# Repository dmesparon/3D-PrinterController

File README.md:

# 3D-PrinterController
3D Printer controller based off ATSAM3X8E with onboard Raspberry PI compute module

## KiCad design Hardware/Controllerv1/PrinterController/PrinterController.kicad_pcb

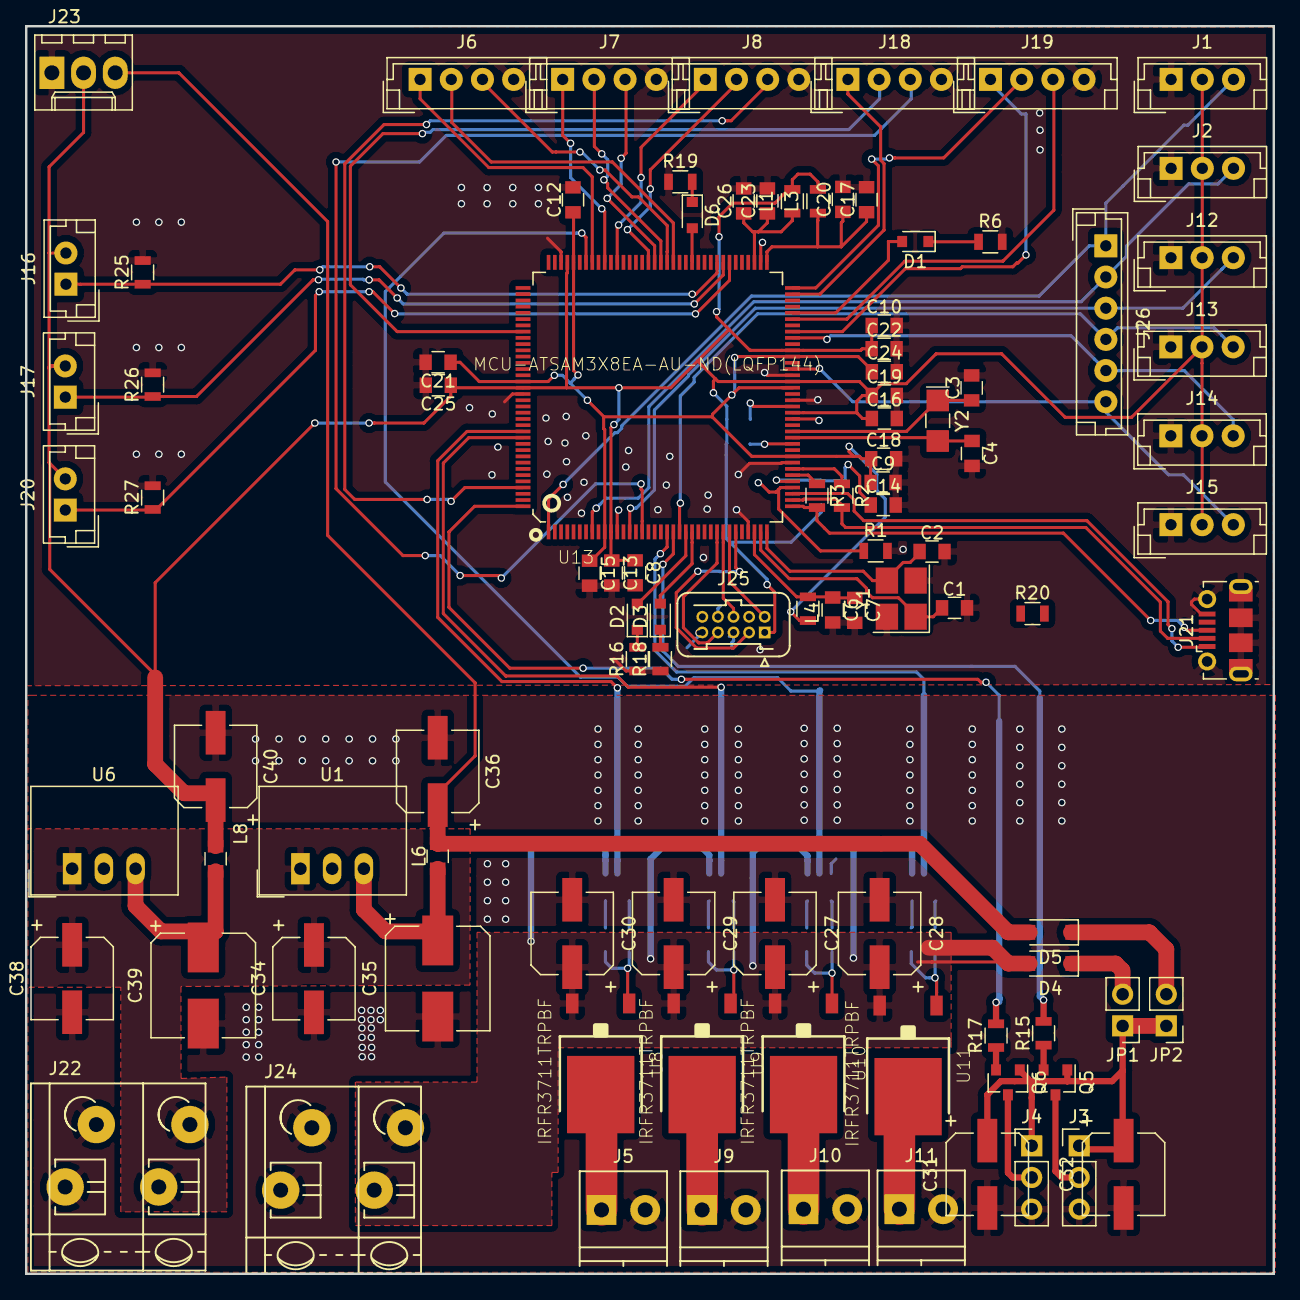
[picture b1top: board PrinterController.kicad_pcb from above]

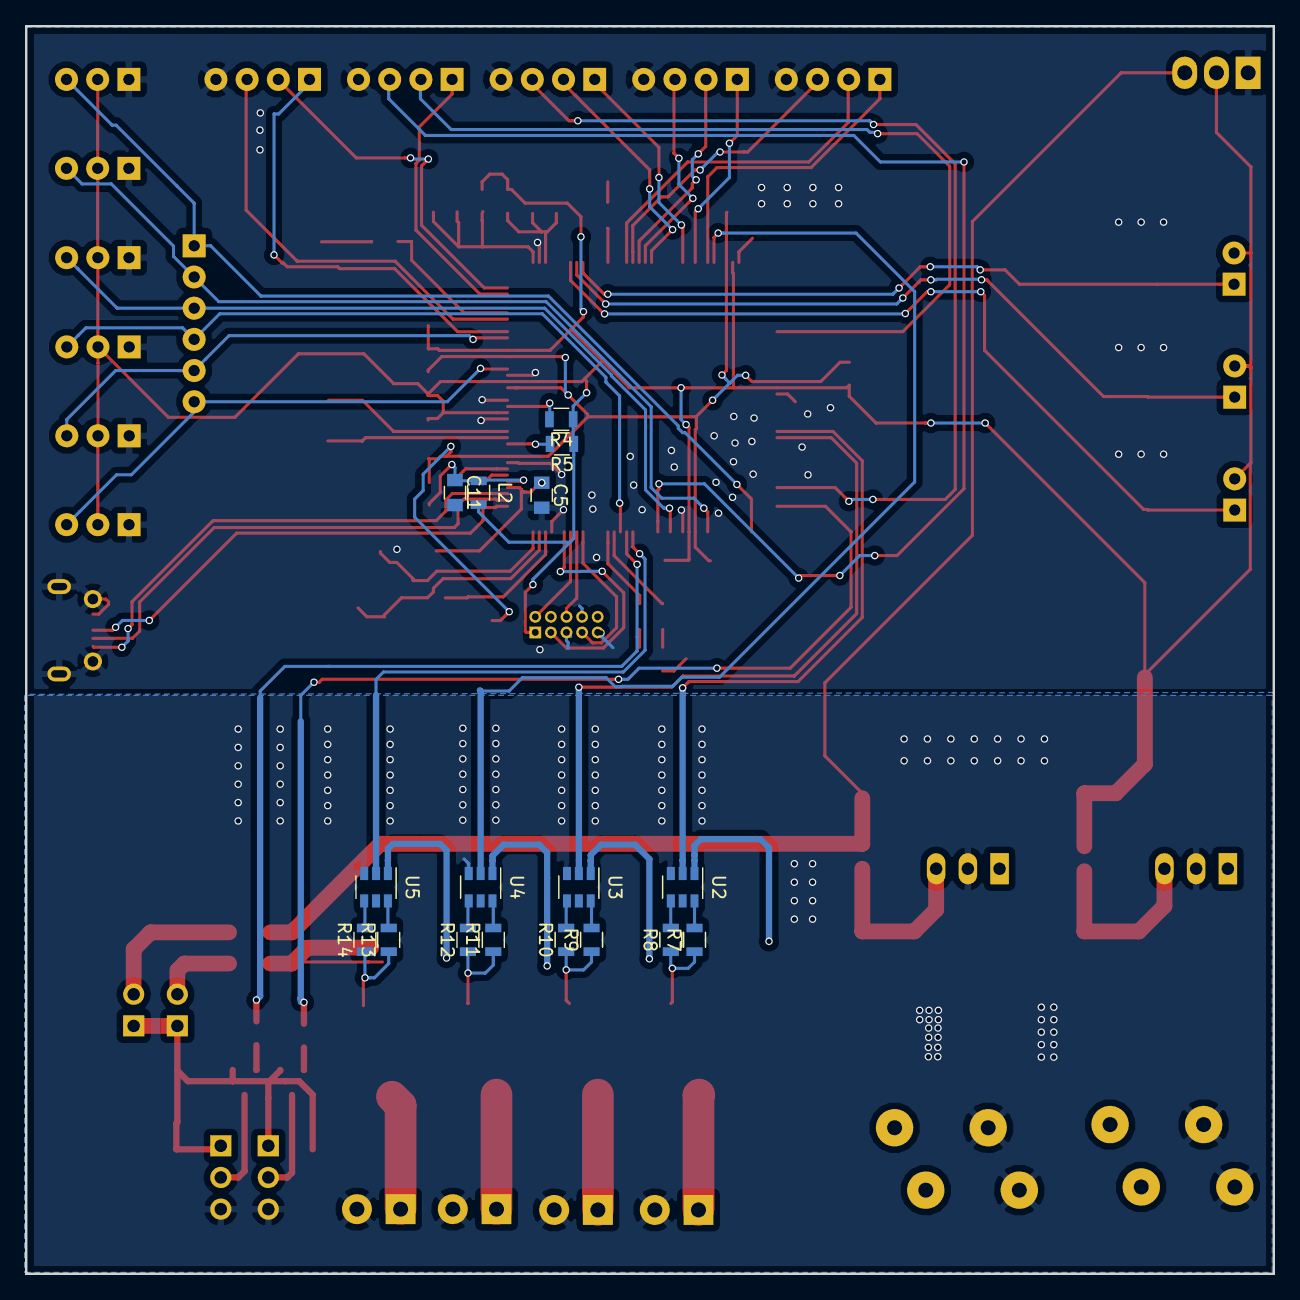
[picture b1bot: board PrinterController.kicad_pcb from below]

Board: 2 copper layers, 100.0 x 100.0 mm, 116 parts (17 on the bottom side), 90 nets.

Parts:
C1, C2, C3, C4: 22p; C_0805
C5: 10p; C_0805
C6, C8, C12, C13, C14, C15, C16, C18, C19, C20, C21, C22, C24, C25, C26: 0.1u; C_0805
C7, C9, C10, C11, C17, C23: 10u; C_0805
C27, C28, C29, C30, C31, C32: 47u; CP_Elec_6.3x5.3
C34, C36, C38, C40: 100u; CP_Elec_6.3x7.7
C35, C39: 470u; CP_Elec_8x10
D1, D2, D3, D6: LED; D_0805
D4, D5: D; D_SOD-123
J1, J2, J12, J13, J14, J15: Conn_01x03; JST_EH_B03B-EH-A_03x2.50mm_Straight
J3, J4: Conn_01x03; Pin_Header_Straight_1x03_Pitch2.54mm
J5, J9, J10, J11: Screw_Terminal_01x02; TerminalBlock_Phoenix_PT-3.5mm_2pol
J6, J7, J8, J18, J19: Conn_01x04; JST_EH_B04B-EH-A_04x2.50mm_Straight
J16, J17, J20: Conn_01x02; JST_EH_B02B-EH-A_02x2.50mm_Straight
J21: USB_OTG; USB_Micro-B_Molex-105017-0001
J22, J24: Screw_Terminal_01x02; TerminalBlock_WAGO-804_RM7.5mm_2pol
J23: Conn_01x03; Molex_KK-6410-03_03x2.54mm_Straight
J25: Conn_ARM_JTAG_SWD_10; Harwin_Gecko-G125-FVX1005L0X_2x05x1.25mm_Straight
J26: Conn_01x06; JST_EH_B06B-EH-A_06x2.50mm_Straight
JP1, JP2: Jumper_NC_Small; Pin_Header_Straight_1x02_Pitch2.54mm
L1, L2, L3, L4: Ferrite_Bead; L_0805
L6, L8: 1u; C_0805
Q5, Q6: Q_NMOS_DGS; SOT-23
R1: 6k8; R_0805
R2, R3: 39; R_0805
R4, R5, R7, R8, R9, R10, R11, R12, R13, R14, R15, R17: 10k; R_0805
R6, R16, R18, R19, R20: 330R; R_0805
R25, R26, R27: 100K; R_0805
U1: R-78E5.0-1.0; DCDC-Conv_RECOM_R-78E-0.5
U2, U3, U4, U5: ZXGD3003E6; SOT-23-6
U6: R-78E3.3-1.0; DCDC-Conv_RECOM_R-78E-0.5
U8, U9, U10, U11: IRFR3711TRPBF; TO252
U13: MCU-ATSAM3X8EA-AU-ND(LQFP144); LQFP144-0.5-20X20M
Y1: Crystal_GND24; Crystal_SMD_3225-4pin_3.2x2.5mm_HandSoldering
Y2: 32.768; Crystal_SMD_MicroCrystal_CC7V-T1A-2pin_3.2x1.5mm_HandSolder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

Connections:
+3V3: C8.1, C10.1, C13.1, C16.1, C19.1, C22.1, C25.1, C40.1, J1.2, J2.2, J12.2, J13.2, J14.2, J15.2, J16.2, J17.2, J20.2, J23.2, J25.1, L1.2, L2.2, L3.2, L8.2, R4.1, R5.1, U13.11, U13.52, U13.57, U13.62, U13.105, U13.125
+5V: C36.1, D5.2, J23.3, L6.2
+VDC: C27.1, C28.1, C29.1, C30.1, D4.2, J24.2, U2.1, U3.1, U4.1, U5.1, U8.2, U9.2, U10.2, U11.2
/DriverStage/FAN1: R15.2, U13.21
/DriverStage/FAN2: R17.2, U13.144
/DriverStage/HEATER1: U2.2, U13.132
/DriverStage/HEATER1_PWR: J5.1, U8.3
/DriverStage/HEATER2: U3.2, U13.133
/DriverStage/HEATER2_PWR: J9.1, U9.3
/DriverStage/HEATER3: U4.2, U13.102
/DriverStage/HEATER3_PWR: J10.1, U10.3
/DriverStage/HEATER4: U5.2, U13.20
/DriverStage/HEATER4_PWR: J11.1, U11.3
/Microcontroller/E0DIR: J18.3, U13.16
/Microcontroller/E0ENABLE: J18.1, U13.71
/Microcontroller/E0STEP: J18.2, U13.116
/Microcontroller/E1DIR: J19.3, U13.67
/Microcontroller/E1ENABLE: J19.1, U13.65
/Microcontroller/E1STEP: J19.2, U13.72
/Microcontroller/TEMP1: J16.1, R25.1, U13.81
/Microcontroller/TEMP2: J17.1, R26.1, U13.80
/Microcontroller/TEMP3: J20.1, R27.1, U13.79
/Microcontroller/VDDANA: C17.1, C20.1, L3.1, U13.73
/Microcontroller/VDDMI: C11.1, C14.1, L2.1, U13.41
/Microcontroller/VDDREF: C23.1, C26.1, L1.1, U13.75
/Microcontroller/XDIR: J6.3, U13.89
/Microcontroller/XENABLE: J6.1, U13.101
/Microcontroller/XSTEP: J6.2, U13.88
/Microcontroller/YDIR: J7.3, U13.91
/Microcontroller/YENABLE: J7.1, U13.99
/Microcontroller/YSTEP: J7.2, U13.90
/Microcontroller/ZDIR: J8.3, U13.141
/Microcontroller/ZENABLE: J8.1, U13.97
/Microcontroller/ZSTEP: J8.2, U13.92
/Motor Connections/ESX1: J1.3, J26.1, U13.1
/Motor Connections/ESX2: J13.3, J26.4, U13.22
/Motor Connections/ESY1: J2.3, J26.2, U13.8
/Motor Connections/ESY2: J14.3, J26.5, U13.64
/Motor Connections/ESZ1: J12.3, J26.3, U13.14
/Motor Connections/ESZ2: J15.3, J26.6, U13.59
GND: C1.2, C2.2, C3.2, C4.2, C5.2, C6.2, C7.2, C8.2, C9.2, C10.2, C11.2, C12.2, C13.2, C14.2, C15.2, C16.2, C17.2, C18.2, C19.2, C20.2, C21.2, C22.2, C23.2, C24.2, C25.2, C26.2, J1.1, J2.1, J6.4, J7.4, J8.4, J12.1, J13.1, J14.1, J15.1, J18.4, J19.4, J21.5, J21.6, J23.1, J25.3, J25.5, J25.9, R1.2, R6.2, R16.1, R18.1, R19.1, R25.2, R26.2, R27.2, U13.12, U13.33, U13.44, U13.51, U13.54, U13.58, U13.74, U13.106, U13.126, Y1.2, Y1.4
GNDPWR: C27.2, C28.2, C29.2, C30.2, C31.2, C32.2, C34.2, C35.2, C36.2, C38.2, C39.2, C40.2, J3.3, J4.3, J5.2, J9.2, J10.2, J11.2, J22.1, J24.1, U1.2, U2.3, U3.3, U4.3, U5.3, U6.2
unnamed: C1.1, U13.35, Y1.1
unnamed: C2.1, U13.36, Y1.3
unnamed: C3.1, U13.49, Y2.1
unnamed: C4.1, U13.48, Y2.2
unnamed: C5.1, R1.1, U13.40
unnamed: C6.1, C7.1, L4.1, U13.34
unnamed: C31.1, C32.1, J3.1, J4.1, JP1.1, JP2.1, Q5.1, Q6.1
unnamed: C35.1, L6.1, U1.3
unnamed: C39.1, L8.1, U6.3
unnamed: D1.1, R6.1
unnamed: D1.2, U13.68
unnamed: D2.1, R16.2
unnamed: D2.2, U13.23
unnamed: D3.1, R18.2
unnamed: D3.2, U13.24
unnamed: D4.1, JP1.2
unnamed: D5.1, JP2.2
unnamed: D6.1, R19.2
unnamed: D6.2, U13.85
unnamed: J3.2, Q5.3
unnamed: J4.2, Q6.3
unnamed: J21.2, R2.2, U13.38
unnamed: J21.3, R3.2, U13.37
unnamed: J25.2, U13.31
unnamed: J25.4, U13.28
unnamed: J25.6, U13.30
unnamed: J25.8, U13.29
unnamed: Q5.2, R15.1
unnamed: Q6.2, R17.1
unnamed: R2.1, U13.43
unnamed: R3.1, U13.42
unnamed: R4.2, U13.53
unnamed: R5.2, U13.47
unnamed: R7.1, R8.1, U8.1
unnamed: R7.2, U2.6
unnamed: R8.2, U2.4
unnamed: R9.2, U3.6
unnamed: R9.1, R10.1, U9.1
unnamed: R10.2, U3.4
unnamed: R11.1, R12.1, U10.1
unnamed: R11.2, U4.6
unnamed: R12.2, U4.4
unnamed: R13.1, R14.1, U11.1
unnamed: R13.2, U5.6
unnamed: R14.2, U5.4
VAA: C34.1, C38.1, J22.2, U1.1, U6.1
VBUS: J21.1, U13.39
VDD: C9.1, C12.1, C15.1, C18.1, C21.1, C24.1, L4.2, U13.10, U13.45, U13.56, U13.61, U13.104, U13.124

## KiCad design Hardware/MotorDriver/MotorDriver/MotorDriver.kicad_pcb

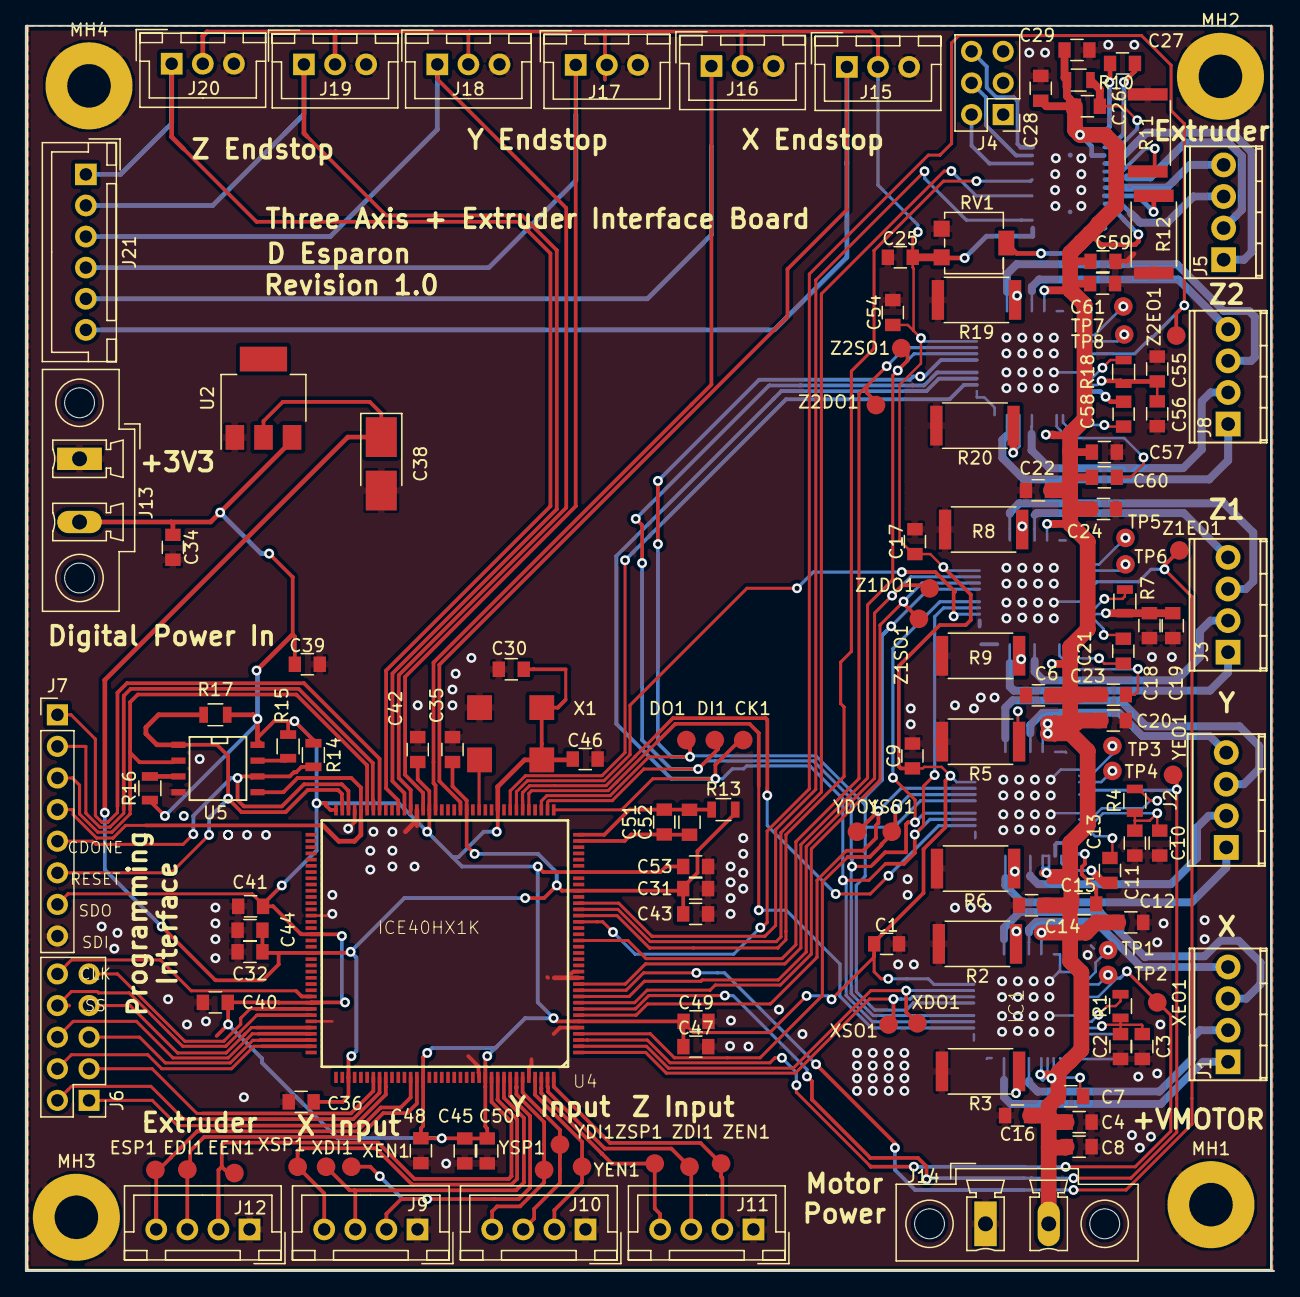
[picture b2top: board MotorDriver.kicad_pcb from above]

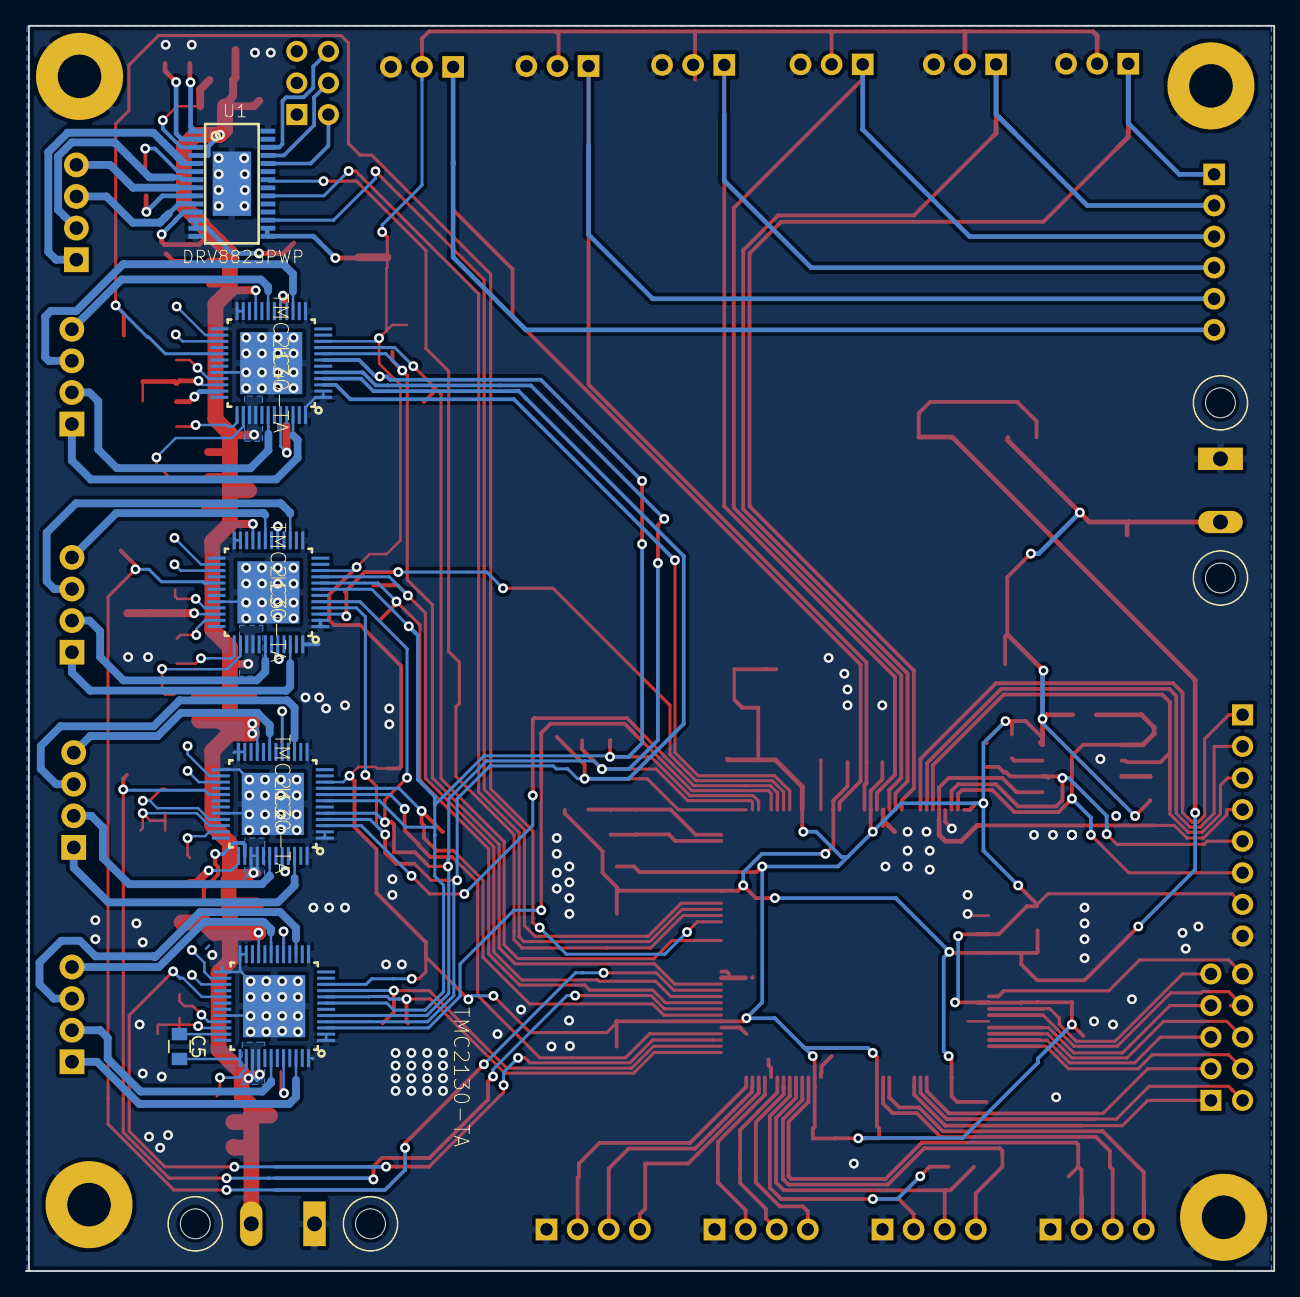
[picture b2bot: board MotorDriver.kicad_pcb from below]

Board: 2 copper layers, 100.1 x 100.1 mm, 149 parts (6 on the bottom side), 130 nets.

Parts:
C1, C9, C17, C25, C29, C30, C31, C32, C35, C36, C39, C40, C41, C42, C46, C48, C49, C50, C52, C53, C54: 0.1u; C_0805
C2, C10, C18, C55: 470n; C_0805
C3, C11, C19, C56: 4.7U; C_0805
C4, C6, C7, C8, C12, C14, C15, C16, C20, C22, C23, C24, C57, C59, C60, C61: 100n; C_0805
C5, C13, C21, C58: 22n; C_0805
C26, C27: 0.01u; C_0805
C28: 100u; C_0805
C34, C43, C44, C45, C47, C51: 10u; C_0805
C38: 100u; CP_Tantalum_Case-B_EIA-3528-21_Hand
CK1: TestPoint; Measurement_Point_Round-SMD-Pad_Small
DI1: TestPoint; Measurement_Point_Round-SMD-Pad_Small
DO1: TestPoint; Measurement_Point_Round-SMD-Pad_Small
EDI1: TestPoint; Measurement_Point_Round-SMD-Pad_Small
EEN1: TestPoint; Measurement_Point_Round-SMD-Pad_Small
ESP1: TestPoint; Measurement_Point_Round-SMD-Pad_Small
IC1, IC2, IC3, IC4: TMC2130-TA; TMC_TQFP48-EP_0.5_7.0X7.0
J1, J2, J3, J5, J8: Screw_Terminal_01x04; TerminalBlock_Phoenix_MPT-2.54mm_4pol
J4: Conn_02x03_Odd_Even; Pin_Header_Straight_2x03_Pitch2.54mm
J6: Conn_02x05_Counter_Clockwise; Pin_Header_Straight_2x05_Pitch2.54mm
J7: Conn_01x08_Male; Pin_Header_Straight_1x08_Pitch2.54mm
J9, J10, J11, J12: Conn_01x04_Female; JST_XH_B04B-XH-A_04x2.50mm_Straight
J13, J14: Screw_Terminal_01x02; PhoenixContact_MCV-GF_02x5.08mm_Vertical_ThreadedFlange_Mou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
J15, J16, J17, J18, J19, J20: Conn_01x03_Male; JST_XH_B03B-XH-A_03x2.50mm_Straight
J21: Conn_01x06_Male; JST_XH_B06B-XH-A_06x2.50mm_Straight
MH1, MH2, MH3, MH4: MountingHole_Pad; MountingHole_3.5mm_Pad
R1, R4, R7, R18: 2.2R; R_0805
R2, R3, R5, R6, R8, R9, R19, R20: 0.15; R_2512
R10, R13: R; R_0805
R11, R12: 0.25; R_2512
R14, R15, R16, R17: 10k; R_0805
RV1: R_POT; Potentiometer_Trimmer_Bourns_3224G
TP1, TP2, TP3, TP4, TP5, TP6, TP7, TP8: Test_Point; Measurement_Point_Round-SMD-Pad_Small
U1: DRV8825PWP; SOP65P640X120-28N.pretty
U2: AZ1117-1.2; SOT-223
U4: ICE40HX1K; TQFP144
U5: M25PX32-VMW; SOIC-8-N
X1: XO32; Oscillator_SMD_EuroQuartz_XO91-4pin_7.0x5.0mm
XDI1: TestPoint; Measurement_Point_Round-SMD-Pad_Small
XDO1: Test_Point; Measurement_Point_Round-SMD-Pad_Small
XEN1: TestPoint; Measurement_Point_Round-SMD-Pad_Small
XEO1: TestPoint; Measurement_Point_Round-SMD-Pad_Small
XSO1: Test_Point; Measurement_Point_Round-SMD-Pad_Small
XSP1: TestPoint; Measurement_Point_Round-SMD-Pad_Small
YDI1: TestPoint; Measurement_Point_Round-SMD-Pad_Small
YDO1: Test_Point; Measurement_Point_Round-SMD-Pad_Small
YEN1: TestPoint; Measurement_Point_Round-SMD-Pad_Small
YEO1: TestPoint; Measurement_Point_Round-SMD-Pad_Small
YSO1: Test_Point; Measurement_Point_Round-SMD-Pad_Small
YSP1: TestPoint; Measurement_Point_Round-SMD-Pad_Small
Z1DO1, Z1SO1, Z2DO1, Z2SO1: Test_Point; Measurement_Point_Round-SMD-Pad_Small
Z1EO1, Z2EO1: TestPoint; Measurement_Point_Round-SMD-Pad_Small
ZDI1: TestPoint; Measurement_Point_Round-SMD-Pad_Small
ZEN1: TestPoint; Measurement_Point_Round-SMD-Pad_Small
ZSP1: TestPoint; Measurement_Point_Round-SMD-Pad_Small

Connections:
+1V2: C31.1, C32.1, C35.1, C36.1, C38.1, C43.1, C44.1, R13.2, U2.2, U4.27, U4.51, U4.92, U4.111
+3V3: C1.1, C9.1, C17.1, C25.2, C30.1, C34.1, C39.1, C40.1, C41.1, C42.1, C45.1, C46.1, C47.1, C48.1, C49.1, C50.1, C53.1, C54.1, IC1.10, IC2.10, IC3.10, IC4.10, J7.7, J13.2, J15.2, J16.2, J17.2, J18.2, J19.2, J20.2, R14.1, R15.1, R16.1, R17.1, RV1.1, U1.15, U1.16, U2.3, U4.6, U4.30, U4.46, U4.57, U4.72, U4.89, U4.100, U4.123, U4.133, U5.8, X1.1, X1.4
+VDC: C4.1, C6.1, C7.1, C8.1, C12.1, C14.1, C15.1, C16.1, C20.1, C22.1, C23.1, C24.1, C26.1, C28.2, C29.2, C57.1, C59.1, C60.1, C61.1, IC1.21, IC1.39, IC1.40, IC2.21, IC2.39, IC2.40, IC3.21, IC3.39, IC3.40, IC4.21, IC4.39, IC4.40, J14.2, R10.2, U1.4, U1.11
/Extruder /DIR: U1.20, U4.24
/Glue Logic/E0DIR: EDI1.1, J12.3, U4.122
/Glue Logic/E0ENABLE: EEN1.1, J12.2, U4.134
/Glue Logic/E0ENABLEO: U1.17, U4.25
/Glue Logic/E0STEP: ESP1.1, J12.4, U4.121
/Glue Logic/E0STEPO: U1.22, U4.23
/Glue Logic/ES1: J15.1, J21.6, U4.52
/Glue Logic/ES2: J16.1, J21.5, U4.56
/Glue Logic/ES3: J17.1, J21.4, U4.58
/Glue Logic/ES4: J18.1, J21.3, U4.60
/Glue Logic/ES5: J19.1, J21.2, U4.61
/Glue Logic/ES6: J20.1, J21.1, U4.62
/Glue Logic/MISO: DO1.1, IC1.7, IC2.7, IC3.7, IC4.7, U4.39
/Glue Logic/MOSI: DI1.1, IC1.5, IC2.5, IC3.5, IC4.5, U4.38
/Glue Logic/SCK: CK1.1, IC1.4, IC2.4, IC3.4, IC4.4, U4.37
/Glue Logic/XDIR: J9.3, U4.136, XDI1.1
/Glue Logic/XENABLE: J9.2, U4.137, XEN1.1
/Glue Logic/XSTEP: J9.4, U4.135, XSP1.1
/Glue Logic/YDIR: J10.3, U4.139, YDI1.1
/Glue Logic/YENABLE: J10.2, U4.141, YEN1.1
/Glue Logic/YSTEP: J10.4, U4.138, YSP1.1
/Glue Logic/ZDIR: J11.3, U4.143, ZDI1.1
/Glue Logic/ZENABLE: J11.2, U4.144, ZEN1.1
/Glue Logic/ZSTEP: J11.4, U4.142, ZSP1.1
/X Driver/CS: IC1.3, U4.41
/X Driver/DIR: IC1.9, U4.2, XDO1.1
/X Driver/ENABLE: IC1.29, U4.3, XEO1.1
/X Driver/STEP: IC1.8, U4.1, XSO1.1
/Y Driver/CS: IC2.3, U4.42
/Y Driver/DIR: IC2.9, U4.7, YDO1.1
/Y Driver/ENABLE: IC2.29, U4.8, YEO1.1
/Y Driver/STEP: IC2.8, U4.4, YSO1.1
/Z Driver 1/CS: IC3.3, U4.43
/Z Driver 1/DIR: IC3.9, U4.10, Z1DO1.1
/Z Driver 1/ENABLE: IC3.29, U4.11, Z1EO1.1
/Z Driver 1/STEP: IC3.8, U4.9, Z1SO1.1
/Z Driver 2/CS: IC4.3, U4.44
/Z Driver 2/DIR: IC4.9, U4.19, Z2DO1.1
/Z Driver 2/ENABLE: IC4.29, U4.22, Z2EO1.1
/Z Driver 2/STEP: IC4.8, U4.12, Z2SO1.1
GND: C1.2, C2.2, C3.2, C4.2, C6.2, C8.2, C9.2, C10.2, C11.2, C12.2, C14.2, C16.2, C17.2, C18.2, C19.2, C20.2, C22.2, C24.2, C25.1, C28.1, C29.1, C30.2, C31.2, C32.2, C34.2, C35.2, C36.2, C38.2, C39.2, C40.2, C41.2, C42.2, C43.2, C44.2, C45.2, C46.2, C47.2, C48.2, C49.2, C50.2, C53.2, C54.2, C55.2, C56.2, C57.2, C59.2, C61.2, IC1.1, IC1.2, IC1.13, IC1.23, IC1.24, IC1.25, IC1.32, IC1.48, IC1.49, IC2.1, IC2.2, IC2.13, IC2.23, IC2.24, IC2.25, IC2.32, IC2.48, IC2.49, IC3.1, IC3.2, IC3.13, IC3.23, IC3.24, IC3.25, IC3.32, IC3.48, IC3.49, IC4.1, IC4.2, IC4.13, IC4.23, IC4.24, IC4.25, IC4.32, IC4.48, IC4.49, J7.8, J9.1, J10.1, J11.1, J12.1, J13.1, J14.1, J15.3, J16.3, J17.3, J18.3, J19.3, J20.3, MH1.1, MH2.1, MH3.1, MH4.1, R2.2, R3.2, R5.2, R6.2, R8.2, R9.2, R11.1, R12.1, R19.2, R20.2, RV1.3, U1.14, U1.28, U1.29, U2.1, U4.5, U4.13, U4.14, U4.59, U4.69, U4.86, U4.103, U4.132, U4.140, U5.4, X1.2
GNDS: C51.2, C52.2, U4.35
unnamed: C2.1, C3.1, IC1.34, R1.1
unnamed: C5.1, IC1.35
unnamed: C5.2, IC1.37
unnamed: C7.2, IC1.38
unnamed: C10.1, C11.1, IC2.34, R4.1
unnamed: C13.1, IC2.35
unnamed: C13.2, IC2.37
unnamed: C15.2, IC2.38
unnamed: C18.1, C19.1, IC3.34, R7.1
unnamed: C21.1, IC3.35
unnamed: C21.2, IC3.37
unnamed: C23.2, IC3.38
unnamed: C26.2, R10.1, U1.3
unnamed: C27.1, U1.2
unnamed: C27.2, U1.1
unnamed: C51.1, C52.1, R13.1, U4.36
unnamed: C55.1, C56.1, IC4.34, R18.1
unnamed: C58.1, IC4.35
unnamed: C58.2, IC4.37
unnamed: C60.2, IC4.38
unnamed: IC1.15, J1.3
unnamed: IC1.17, R2.1
unnamed: IC1.19, J1.4
unnamed: IC1.26, TP1.1
unnamed: IC1.27, TP2.1
unnamed: IC1.33, R1.2
unnamed: IC1.42, J1.2
unnamed: IC1.44, R3.1
unnamed: IC1.46, J1.1
unnamed: IC2.15, J2.3
unnamed: IC2.17, R5.1
unnamed: IC2.19, J2.4
unnamed: IC2.26, TP3.1
unnamed: IC2.27, TP4.1
unnamed: IC2.33, R4.2
unnamed: IC2.42, J2.2
unnamed: IC2.44, R6.1
unnamed: IC2.46, J2.1
unnamed: IC3.15, J3.3
unnamed: IC3.17, R8.1
unnamed: IC3.19, J3.4
unnamed: IC3.26, TP5.1
unnamed: IC3.27, TP6.1
unnamed: IC3.33, R7.2
unnamed: IC3.42, J3.2
unnamed: IC3.44, R9.1
unnamed: IC3.46, J3.1
unnamed: IC4.15, J8.3
unnamed: IC4.17, R19.1
unnamed: IC4.19, J8.4
unnamed: IC4.26, TP7.1
unnamed: IC4.27, TP8.1
unnamed: IC4.33, R18.2
unnamed: IC4.42, J8.2
unnamed: IC4.44, R20.1
unnamed: IC4.46, J8.1
unnamed: J4.2, U1.24
unnamed: J4.4, U1.25
unnamed: J4.6, U1.26
unnamed: J5.1, U1.5
unnamed: J5.2, U1.7
unnamed: J5.3, U1.10
unnamed: J5.4, U1.8
unnamed: J6.1, U4.117
unnamed: J6.2, U4.116
unnamed: J6.3, U4.115
unnamed: J6.4, U4.107
unnamed: J6.5, U4.106
unnamed: J6.6, U4.105
unnamed: J6.7, U4.104
unnamed: J6.8, U4.102
unnamed: J6.9, U4.101
unnamed: J6.10, U4.99
unnamed: J7.1, U4.65
unnamed: J7.2, U4.66
unnamed: J7.3, U4.67, U5.2
unnamed: J7.4, U4.68, U5.5
unnamed: J7.5, R14.2, U4.70, U5.6
unnamed: J7.6, R17.2, U4.71, U5.1
unnamed: R11.2, U1.6
unnamed: R12.2, U1.9
unnamed: R15.2, U5.7
unnamed: R16.2, U5.3
unnamed: RV1.2, U1.12, U1.13
unnamed: U4.49, X1.3

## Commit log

2018-06-12 Added first RPI Module schematics
2018-06-14 Added version 1 hardware schematic files
2018-06-14 Added LAN9514 chipset
2018-06-16 Added main controller and Power Outputs
2018-06-24 Added updates to PCB
2018-06-28 Added pcb changes
2018-06-29 Updated PCBS
2018-07-08 Added Motor driver circuitry
2018-07-14 Added routed Power switching circuitry
2018-07-15 Added additional PCB layout
2018-07-26 Added updates to Motor Driver Hardware
2018-07-29 Added almost completed Motor Driver design
2018-08-10 Added Motor driver revision 1.0
2018-08-10 Added updates to controller hardware
2018-08-11 Library update for ATSAM
